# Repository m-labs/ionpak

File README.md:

ionpak
======

A modern, low-cost universal controller for hot-cathode ionization vacuum gauges.

Why?
----

Many physics experiments require a good vacuum and therefore tools to diagnose vacuum-related problems. Ionization gauges provide a way to measure pressures in the medium to ultra-high vacuum regimes.

While the gauges themselves can be procured quite easily, the controller situation is more problematic. Existing commercial and DIY solutions have one or more of the following issues:

 * expensive
 * proprietary
 * poor performance at low (pA) collector currents
 * designed with obsolete components and overly bulky
 * lack of gauge voltage/current programmability
 * no/poor connectivity to a logging database
 * poor design and construction

The ionpak features:

 * a single-board low-cost design with modern components
 * open hardware and software
 * sub-pA electrometer performance
 * configurable voltages and emission current to adapt to various gauges
 * Ethernet connectivity

Where to find ionization vacuum gauges?
---------------------------------------

For medium and high vacuum, Chinese gauges can be ordered on Taobao under references ZJ-27 and ZJ-10. The Chinese for ionization gauge is 电离规. Those gauges have a simple construction and an extremely low cost, under USD 10 for glass tubulated models (requires flameworking) and a few times that price for flange-mounted ones. Those manufactured by [Chengdu Zhenghua](http://www.zhvacuum.com) appear to work satisfactorily, and glass gauges arrive sealed under vacuum (around 10⁻⁵ to 10⁻⁶ mbar) so they can be tested immediately. Ceramic sockets for the gauges can often be ordered from the same Taobao vendor.

For ultra-high vacuum, you can use G8130 from KJLC, which is pricy but of excellent quality. There is a lower-cost Bayard-Alpert Chinese gauge ZJ-12, of dubious quality for those pressure ranges, and with 2.5x less sensitivity than the KJLC part.

A low-cost source of quality UHV gauges remains to be found. You can try eBay, but the condition of the items is highly random.

How to connect the gauge?
-------------------------

The collector must be connected with a shielded (e.g. coaxial) cable. If the gauge has a metallic body (e.g. gauges mounted on CF flanges), connect the shield of the cable to the body, so that current from the high voltage electrodes will not leak into the collector electrode. This should not cause any ground loop in your system, as the gauge circuits inside the ionpak are galvanically isolated from its power input and from its Ethernet connector.

If a single cable is used for the filament and anode connections, the anode wire must be particularly well insulated from the filament wires, to avoid leakage currents that can be significant when the gauge is operated with a low emission (100µA or less) and influence the measurement result.

"Domino" terminal blocks from the local hardware store, with the plastic removed, can be used to connect the cables to the pins of CF-flanged gauges. Female circular contacts, such as Amphenol AT62-16-0122, are a nicer alternative but are slightly harder to find.

For baked systems, use PTFE insulated cables that can withstand 200°C. Operating the gauge during bake-out can remove the need to degas it (see the paper [Comments on the stability of B-A ionization gages](https://www.nist.gov/sites/default/files/documents/calibrations/jv13-2.pdf)).

It is a good idea to attach the cables to the vacuum system with a strap to avoid damaging the gauge by accidentally pulling on the cables, and to place a cover onto the pins to reduce the electrical shock hazard from the high voltage. Preferably those items should be made of metal so that they can be left on during bakeout.

Using the ionpak
----------------
Connect the ionpak to a firewalled Ethernet network *only*, as it does not provide authentication over the network.

The ionpak has a static IP address that defaults to `192.168.69.1`. It has a self-explanatory web interface that you can access by pointing your browser to [http://192.168.69.1](http://192.168.69.1). By default, the controller is disabled and the ionpak will not produce any output voltages; use the web interface to input your gauge settings and enable the controller.

The IP address, along with all the other configuration options, can be reset to the defaults by holding the pushbutton while the ionpak is powering up. The status LED will flash rapidly to acknowledge the configuration reset.

In addition to displaying its measurement results in the web interface, the ionpak exports them in the JSON format. The results are very straightforward to access from Python:

```
>>> import requests
>>> import json
>>> json.loads(requests.get("http://192.168.69.1/measure.json").text)
{'pressure': 3.8e-06, 'current': 3.357e-08}
```

In the JSON document, `pressure` is expressed in millibars and `current` (through the collector input) is expressed in amperes.

Warning
-------

Ionization gauges use dangerous voltages and the ionpak is capable of delivering a lethal amount of power. Be careful and use at your own risk.

Building and loading the firmware
---------------------------------

```sh
cd firmware
cargo build --release
openocd -f openocd.cfg
```

License
-------

Copyright 2017 M-Labs Limited.

License TBD, probably will be CERN OHL and GPL.

Pictures in the ``pictures`` folder, except ``proto_rev1.jpg``, are copyright Michelle Poon and not free.

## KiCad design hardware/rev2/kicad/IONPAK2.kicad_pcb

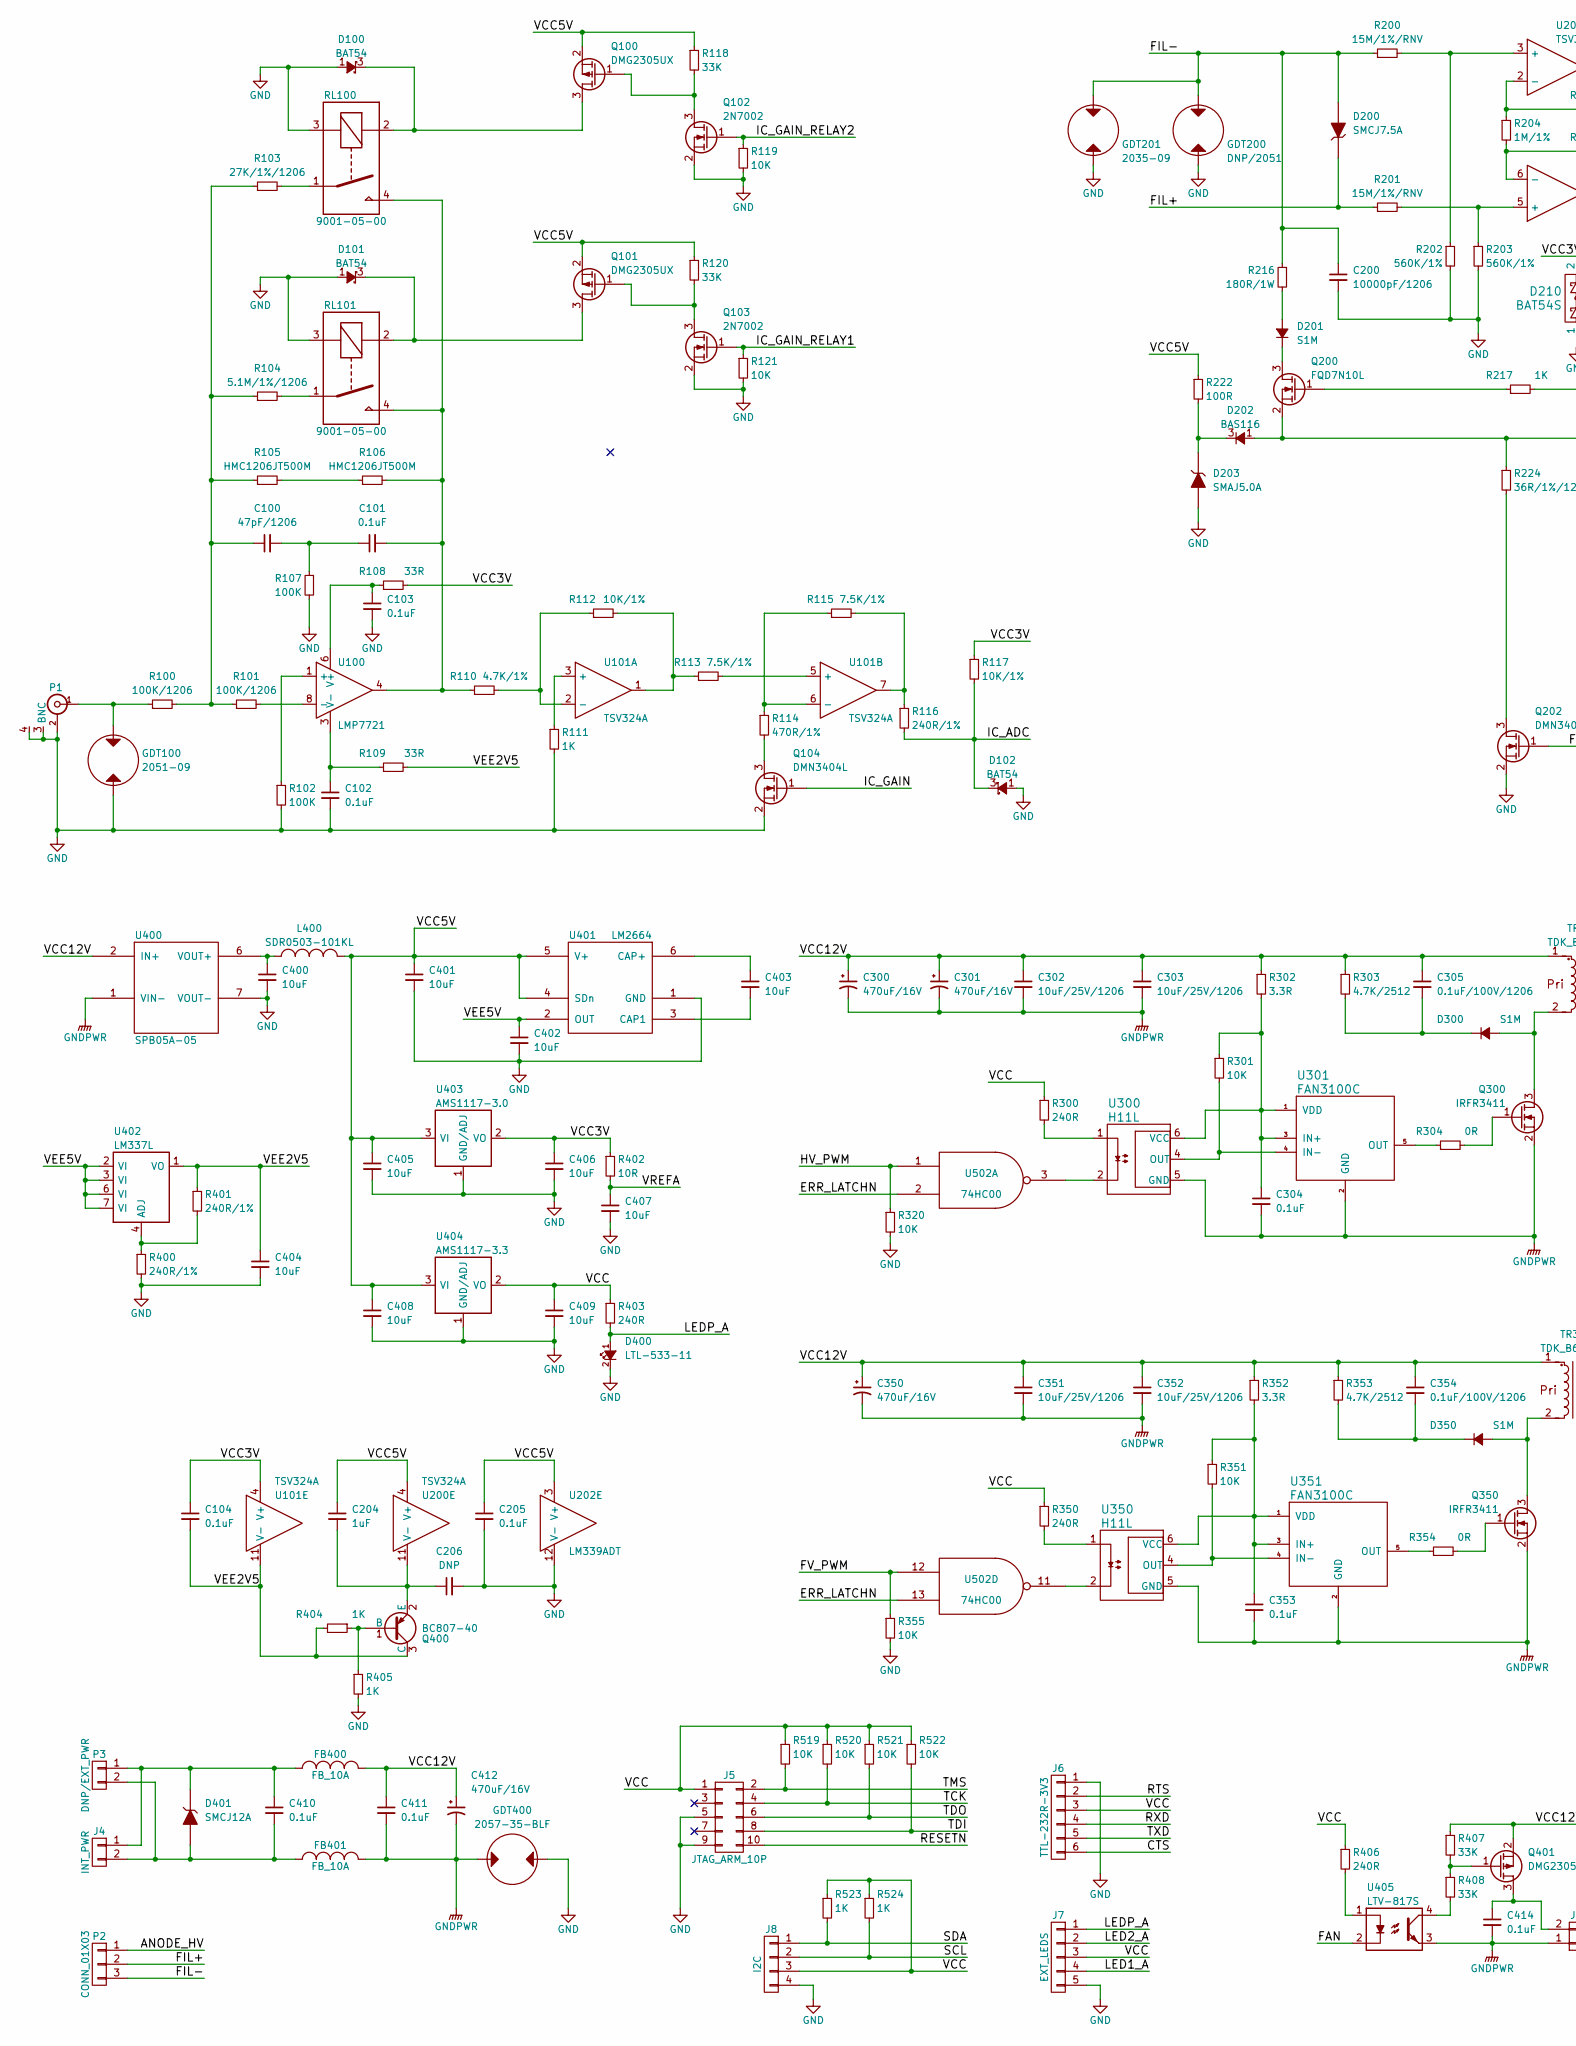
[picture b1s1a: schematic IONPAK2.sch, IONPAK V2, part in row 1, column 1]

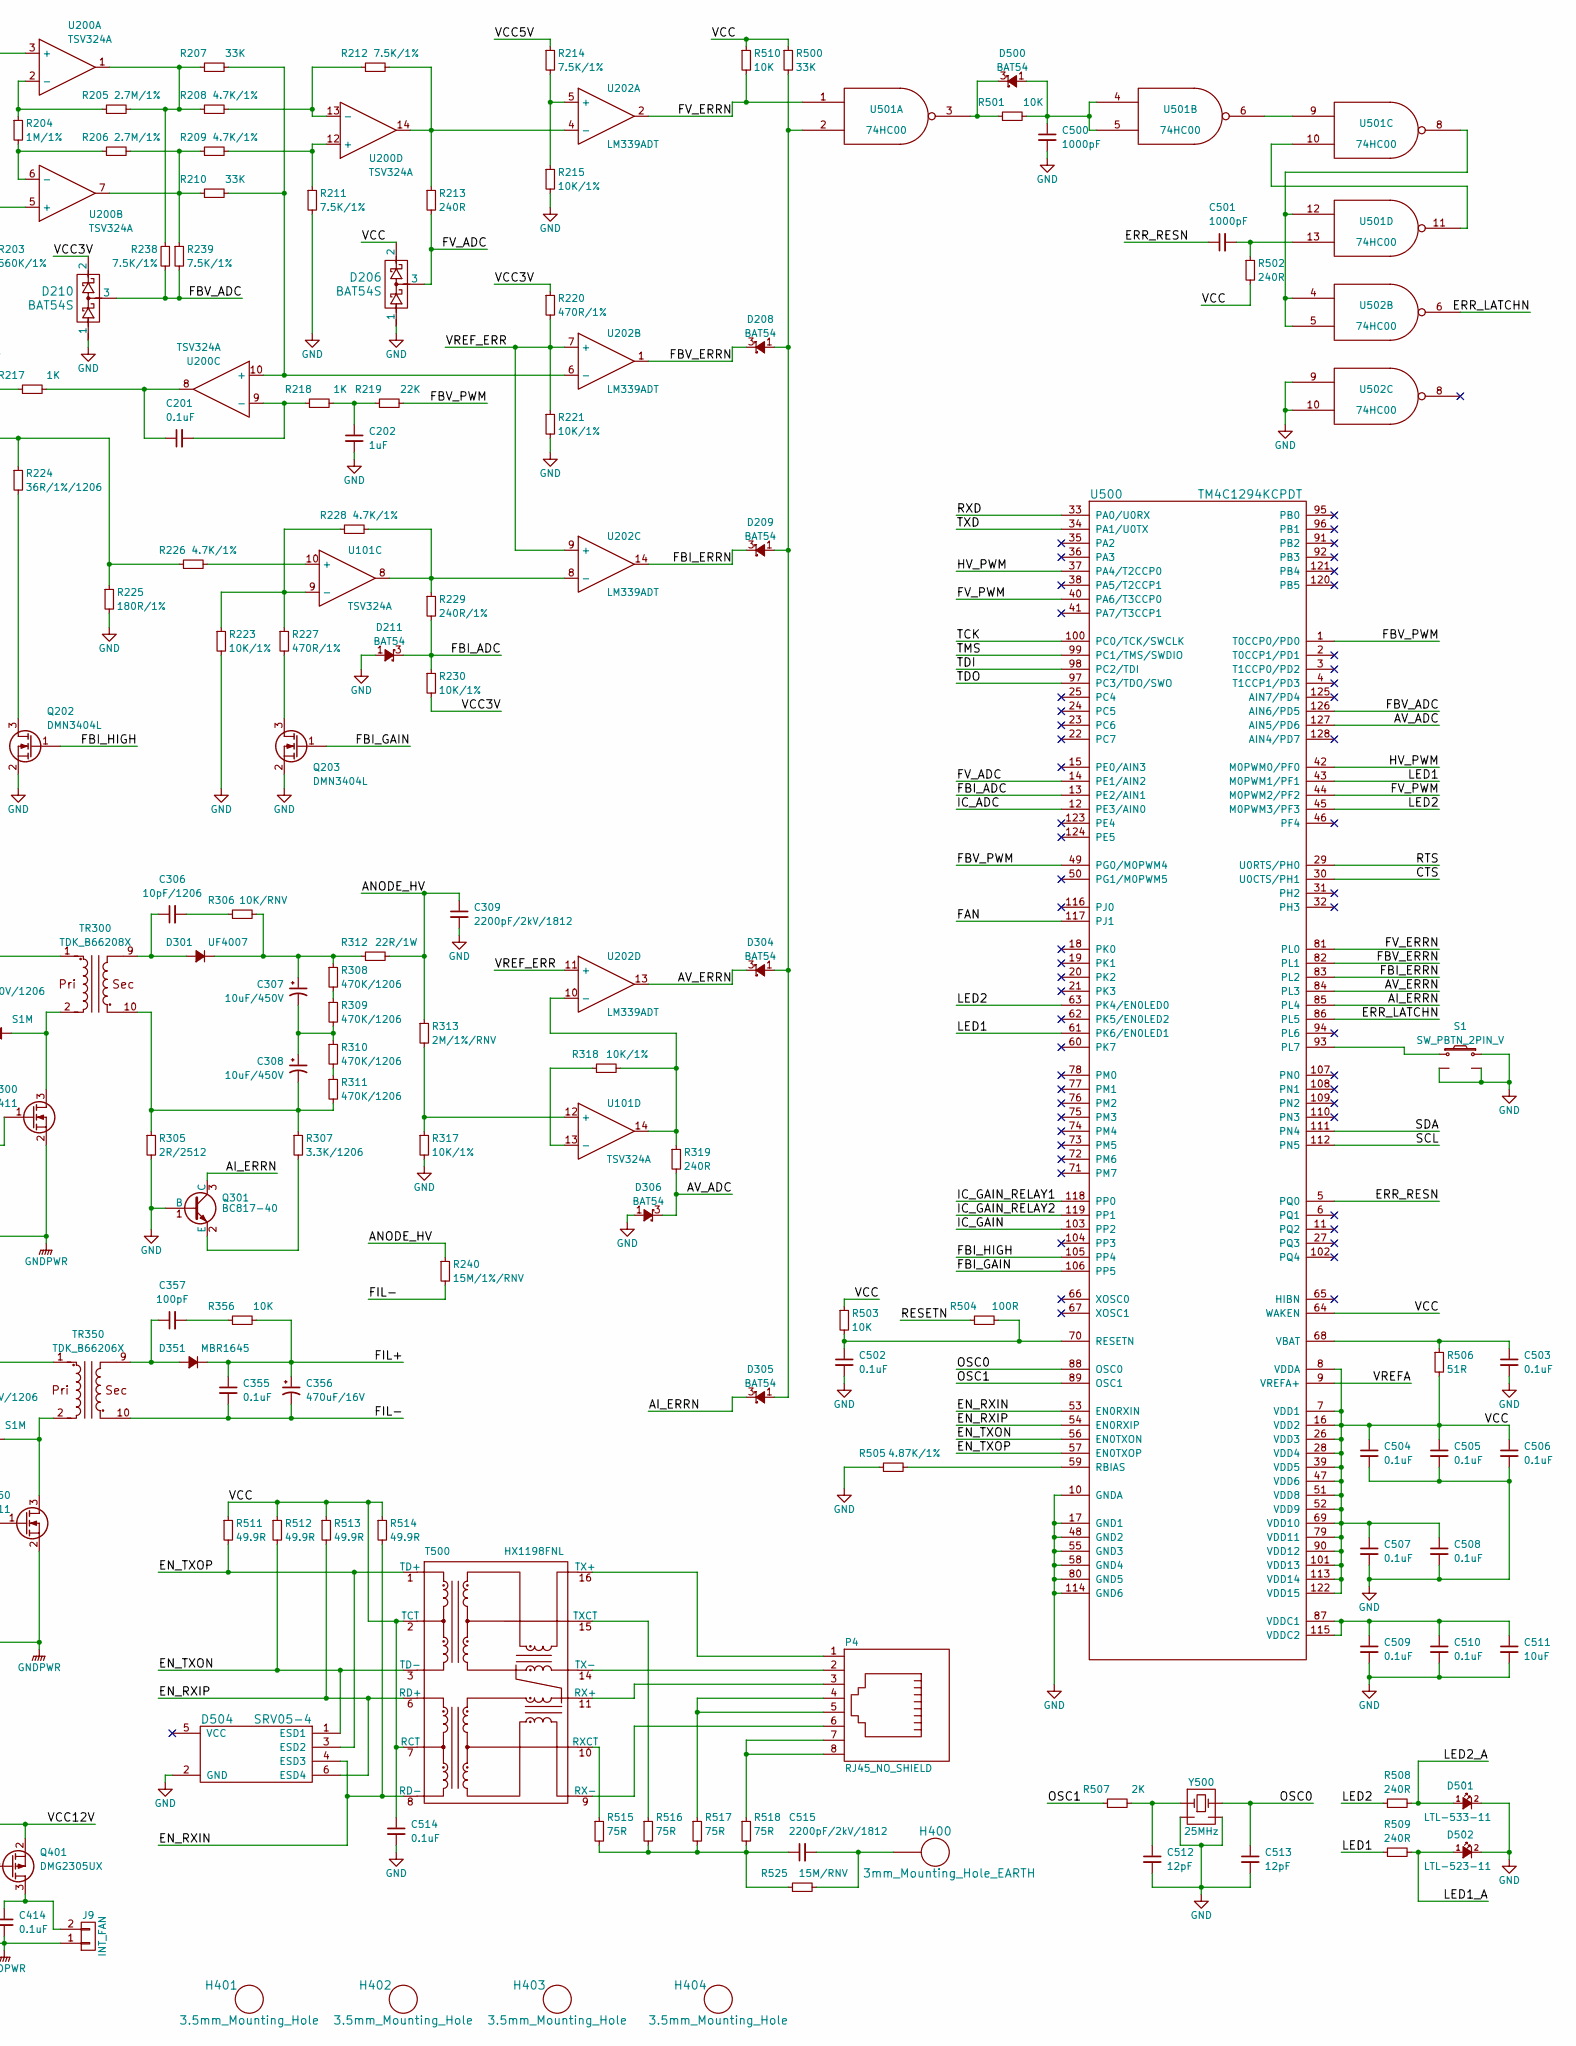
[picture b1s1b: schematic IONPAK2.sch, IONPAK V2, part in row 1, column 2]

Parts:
C100: 47pF/1206; C_1206_ns; MPN 12062A101JAT2A
C101, C102, C103, C104, C201, C205, C304, C353, C355, C410, C411, C414, C502, C503, C504, C505, C506, C507, C508, C509, C510, C514: 0.1uF; C_0603; MPN GRM188R71C104JA01D
C200: 10000pF/1206; C_1206; MPN GRM31BR72J103KW01L
C202, C204: 1uF; C_0603; MPN GRM188R60J105KA01J
C206: DNP; C_0603
C300, C301, C350, C356, C412: 470uF/16V; C_Radial_D13_L21_P5; MPN ECA-1CM471
C302, C303, C351, C352: 10uF/25V/1206; C_1206; MPN CL31A106KAHNNNE
C305, C354: 0.1uF/100V/1206; C_1206; MPN GRJ319R72A104KE11L
C306: 10pF/1206; C_1206; MPN CL31C100JIFNNNE
C307, C308: 10uF/450V; C_Radial_D14_L25_P5; MPN UVR2W100MHD1TO
C309, C515: 2200pF/2kV/1812; C_1812; MPN C1812C222KGRACTU
C357: 100pF; C_0603; MPN GRM0335C1E101JA01D
C400, C401, C402, C403, C404, C405, C406, C407, C408, C409, C511: 10uF; C_0603; MPN GRM188R60J106KE47D
C500, C501: 1000pF; C_0603; MPN GRM033R71C102KA01D
C512, C513: 12pF; C_0603; MPN GRM0335C1E120JA01D
D100, D101, D102, D208, D209, D211, D304, D305, D306, D500: BAT54; SOT-23; MPN BAT54SLT1G
D200: SMCJ7.5A; DO-214AB; MPN SMCJ7.5A-13-F
D201, D300, D350: S1M; DO-214AC; MPN S1MTR
D202: BAS116; SOT-23; MPN BAS116-7-F
D203: SMAJ5.0A; DO-214AC; MPN SMAJ5.0A
D206, D210: BAT54S; SOT-23; MPN BAT54SLT1G
D301: UF4007; Diode_DO-41_SOD81_Horizontal_RM10; MPN UF4007TA
D351: MBR1645; TO220AC; MPN MBR1060
D400, D501: LTL-533-11; LED_D3.0mm_Horizontal_O3.81mm_Z10.0mm; MPN LTL-533-11
D401: SMCJ12A; DO-214AB; MPN SMCJ12A-13-F
D502: LTL-523-11; LED_D3.0mm_Horizontal_O3.81mm_Z10.0mm; MPN LTL-523-11
D504: SRV05-4; SOT-23-6; MPN SRV05-4ATR
FB400, FB401: FB_10A; 28F0121-0SR-10; MPN 28F0121-0SR-10
GDT100: 2051-09; BOURNS-GDT-2051_ns; MPN 2051-09-SM-RPLF
GDT200: DNP/2051; BOURNS-GDT-2051
GDT201: 2035-09; BOURNS-GDT-2035TH; MPN 2035-09-BT1LF
GDT400: 2057-35-BLF; BOURNS-GDT-2035TH; MPN 2057-35-BLF
H400: 3mm_Mounting_Hole_EARTH; 3mm_EARTH
H401, H402, H403, H404: 3.5mm_Mounting_Hole; NPTH_3mm5_ID
J4: INT_PWR; PhoenixContact_MCV-G_02x5.08mm_Vertical; MPN 1836299
J5: JTAG_ARM_10P; Pin_Header_Straight_2x05_Pitch1.27mm; MPN GRPB052VWVN-RC
J6: TTL-232R-3V3; Pin_Header_Straight_1x06_Pitch2.54mm; MPN SWR25X-NRTC-S06-ST-BA
J7: EXT_LEDS; Pin_Header_Straight_1x05_Pitch2.54mm; MPN SWR25X-NRTC-S04-ST-BA
J8: I2C; Pin_Header_Straight_1x04_Pitch2.54mm
J9: INT_FAN; Molex_KK-6410-02_02x2.54mm_Straight; MPN 0022272021
L400: SDR0503-101KL; Choke_SMD_Wuerth-WE-PD2-Typ-MS; MPN SDR0503-101KL
P1: BNC; bnc_90_1-1337543-0_ns; MPN 1-1337543-0
P2: CONN_01X03; PhoenixContact_1786417_03; MPN 1786417
P3: DNP/EXT_PWR; PhoenixContact_MSTBA-G_02x5.08mm_Angled
P4: RJ45_NO_SHIELD; FCI_54601-908WPLF; MPN 54601-908WPLF
Q100, Q101, Q401: DMG2305UX; SOT-23; MPN DMG2305UX-13
Q102, Q103: 2N7002; SOT-23; MPN 2N7002P,215
Q104, Q202, Q203: DMN3404L; SOT-23; MPN DMN3404L-7
Q200: FQD7N10L; DPAK; MPN FQD7N10LTM
Q300, Q350: IRFR3411; DPAK; MPN IRFR3411TRPBF
Q301: BC817-40; SOT-23; MPN BC81740MTF
Q400: BC807-40; SOT-23; MPN BC807-40LT1G
R100, R101: 100K/1206; R_1206_ns; MPN RC1206JR-07100KL
R102, R107: 100K; R_0603; MPN RC0603JR-07100KL
R103: 27K/1%/1206; R_1206_ns; MPN RC1206FR-0727KL
R104: 5.1M/1%/1206; R_1206_ns; MPN RC1206FR-0727KL
R105, R106: HMC1206JT500M; R_1206_ns; MPN HMC1206JT500M
R108, R109: 33R; R_0603; MPN RC0603FR-0733RL
R110, R208, R209, R226, R228: 4.7K/1%; R_0603; MPN RC0603FR-074K7L
R111, R217, R218, R404, R405, R523, R524: 1K; R_0603; MPN RC0603FR-071KL
R112, R117, R215, R221, R223, R230, R317, R318: 10K/1%; R_0603; MPN RC0603FR-0710KL
R113, R115, R211, R212, R214, R238, R239: 7.5K/1%; R_0603; MPN RC0603FR-077K5L
R114, R220, R227: 470R/1%; R_0603; MPN RC0603FR-07470RL
R116, R229, R400, R401: 240R/1%; R_0603; MPN RC0603FR-07240RL
R118, R120, R207, R210, R407, R408, R500: 33K; R_0603; MPN RC0603FR-0733KL
R119, R121, R301, R320, R351, R355, R356, R501, R503, R510, R519, R520, R521, R522: 10K; R_0603; MPN RC0603FR-0710KL
R200, R201, R240: 15M/1%/RNV; R_Axial_DIN0207_L6.3mm_D2.5mm_P10.16mm_Horizontal; MPN RNV14FAL15M0
R202, R203: 560K/1%; R_0603; MPN RC0603FR-07560KL
R204: 1M/1%; R_0603; MPN RC0603FR-071ML
R205, R206: 2.7M/1%; R_0603; MPN RC0603FR-072M7L
R213, R300, R319, R350, R403, R406, R502, R508, R509: 240R; R_0603; MPN RC0603FR-07240RL
R216: 180R/1W; R_Axial_DIN0414_L11.9mm_D4.5mm_P15.24mm_Horizontal; MPN KNP100JR-73-180R
R219: 22K; R_0603; MPN RC0603FR-0722KL
R222, R504: 100R; R_0603; MPN RC0603JR-07100RL
R224: 36R/1%/1206; R_1206; MPN RC1206FR-0736RL
R225: 180R/1%; R_0603; MPN RC0603FR-07180RL
R302, R352: 3.3R; R_0603; MPN RC0603FR-073R3L
R303, R353: 4.7K/2512; R_2512; MPN RC2512JK-074K7L
R304, R354: 0R; R_0603; MPN RC0603JR-070RL
R305: 2R/2512; R_2512; MPN RMCF2512JT2R00
R306: 10K/RNV; R_Axial_DIN0207_L6.3mm_D2.5mm_P10.16mm_Horizontal; MPN RNF14FTD10K0
R307: 3.3K/1206; R_1206; MPN RC1206JR-073K3L
R308, R309, R310, R311: 470K/1206; R_1206; MPN RC1206JR-07470KL
R312: 22R/1W; R_Axial_DIN0414_L11.9mm_D4.5mm_P15.24mm_Horizontal; MPN KNP100JR-73-22R
R313: 2M/1%/RNV; R_Axial_DIN0207_L6.3mm_D2.5mm_P10.16mm_Horizontal; MPN RNV14FAL2M00
R402: 10R; R_0603; MPN RC0603JR-0710RL
R505: 4.87K/1%; R_0603; MPN RC0603FR-074K87L
R506: 51R; R_0603; MPN RC0603FR-0751RL
R507: 2K; R_0603; MPN RC0603FR-072KL
R511, R512, R513, R514: 49.9R; R_0603; MPN RC0603FR-0749R9L
R515, R516, R517, R518: 75R; R_0603; MPN 311-75.0HRCT-ND
R525: 15M/RNV; R_Axial_DIN0207_L6.3mm_D2.5mm_P10.16mm_Horizontal; MPN RNV14FAL15M0
RL100, RL101: 9001-05-00; COTO-9001_ns; MPN 9001-05-00
S1: SW_PBTN_2PIN_V; SW_Tactile_SKHH_Angled_v; MPN 1825027-8
T500: HX1198FNL; H2019FNL; MPN HX1198FNL
TR300: TDK_B66208X; MPN TranformerFl
TR350: TDK_B66206X; MPN TransformerHV
U100: LMP7721; SOIC-8-N_ns; MPN LMP7721MA/NOPB
U101, U200: TSV324A; SOIC-14_N; MPN TSV324IDT
U202: LM339ADT; SOIC-14_N; MPN LM339ADT
U300, U350: H11L; 6-SMD; MPN H11L1S(TA)
U301, U351: FAN3100C; SOT-23-5; MPN FAN3100CSX
U400: SPB05A-05; SPB05A; MPN SPB05A-05
U401: LM2664; SOT-23-6; MPN LM2664M6/NOPB
U402: LM337L; SOIC-8-N; MPN LM337LMX
U403: AMS1117-3.0; SOT-223; MPN TLV1117LV30DCYR
U404: AMS1117-3.3; SOT-223; MPN AZ1117IH-3.3TRG1
U405: LTV-817S; OPTO-SMD4; MPN LTV-817S-TA1
U500: TM4C1294KCPDT; TQFP-128; MPN TM4C1294KCPDTI3R
U501, U502: 74HC00; SOIC-14_N; MPN 74HC00S14-13
Y500: 25MHz; XTAL3_2X2_5; MPN NX3225GA-25.000M-STD-CRG-2

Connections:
/AI_ERRN: D305.3 (K), Q301.3 (C), U500.85 (PL4)
/ANODE_HV: C309.1, P2.1, R240.1, R312.2, R313.1
/AV_ADC: D306.3 (K), R319.2, U500.127 (AIN5/PD6)
/AV_ERRN: D304.3 (K), U202.13, U500.84 (PL3)
/CTS: J6.6, U500.30 (U0CTS/PH1)
/EN_RXIN: D504.4 (ESD3), R514.2, T500.8 (RD-), U500.53 (EN0RXIN)
/EN_RXIP: D504.6 (ESD4), R513.2, T500.6 (RD+), U500.54 (EN0RXIP)
/EN_TXON: D504.1 (ESD1), R512.2, T500.3 (TD-), U500.56 (EN0TXON)
/EN_TXOP: D504.3 (ESD2), R511.2, T500.1 (TD+), U500.57 (EN0TXOP)
/ERR_LATCHN: U500.86 (PL5), U502.2, U502.6, U502.13
/ERR_RESN: C501.1, U500.5 (PQ0)
/FAN: U405.2, U500.117 (PJ1)
/FBI_ADC: D211.3 (K), R229.2, R230.1, U500.13 (PE2/AIN1)
/FBI_ERRN: D209.3 (K), U202.14, U500.83 (PL2)
/FBI_GAIN: Q203.1 (G), U500.106 (PP5)
/FBI_HIGH: Q202.1 (G), U500.105 (PP4)
/FBV_ADC: D210.3, R238.2, R239.2, U500.126 (AIN6/PD5)
/FBV_ERRN: D208.3 (K), U202.1, U500.82 (PL1)
/FBV_PWM: R219.2, U500.1 (T0CCP0/PD0), U500.49 (PG0/M0PWM4)
/FIL+: C355.1, C356.1, D200.1 (K), D351.1 (K), P2.2, R201.1, R356.2
/FIL-: C200.1, C355.2, C356.2, D200.2 (A), GDT200.1, GDT201.1, P2.3, R200.1, R216.1, R240.2, TR350.10
/FV_ADC: D206.3, R213.2, U500.14 (PE1/AIN2)
/FV_ERRN: R510.2, U202.2, U500.81 (PL0), U501.1
/FV_PWM: R355.1, U500.40 (PA6/T3CCP0), U500.44 (M0PWM2/PF2), U502.12
/HV_PWM: R320.1, U500.37 (PA4/T2CCP0), U500.42 (M0PWM0/PF0), U502.1
/IC_ADC: D102.3 (K), R116.2, R117.2, U500.12 (PE3/AIN0)
/IC_GAIN: Q104.1 (G), U500.103 (PP2)
/IC_GAIN_RELAY1: Q103.1 (G), R121.1, U500.118 (PP0)
/IC_GAIN_RELAY2: Q102.1 (G), R119.1, U500.119 (PP1)
/LED1: R509.1, U500.43 (M0PWM1/PF1), U500.61 (PK6/EN0LED1)
/LED1_A: D502.1 (A), J7.4, R509.2
/LED2: R508.1, U500.45 (M0PWM3/PF3), U500.63 (PK4/EN0LED0)
/LED2_A: D501.1 (A), J7.2, R508.2
/LEDP_A: D400.1 (A), J7.1, R403.2
/OSC0: C513.1, U500.88 (OSC0), Y500.3
/OSC1: R507.1, U500.89 (OSC1)
/RESETN: J5.10, R504.1
/RTS: J6.2, U500.29 (U0RTS/PH0)
/RXD: J6.4, U500.33 (PA0/U0RX)
/SCL: J8.2, R524.2, U500.112 (PN5)
/SDA: J8.1, R523.2, U500.111 (PN4)
/TCK: J5.4, R520.2, U500.100 (PC0/TCK/SWCLK)
/TDI: J5.8, R522.2, U500.98 (PC2/TDI)
/TDO: J5.6, R521.2, U500.97 (PC3/TDO/SWO)
/TMS: J5.2, R519.2, U500.99 (PC1/TMS/SWDIO)
/TXD: J6.5, U500.34 (PA1/U0TX)
/VCC3V: C104.1, C406.1, D210.2, R108.2, R117.1, R220.1, R230.2, R402.1, U101.4 (V+), U403.2 (VO)
/VCC5V: C204.1, C205.1, C401.1, C405.1, C408.1, L400.2, Q100.2 (S), Q101.2 (S), R118.1, R120.1, R214.1, R222.1, U200.4 (V+), U202.3 (V+), U401.4 (SDn), U401.5 (V+), U403.3 (VI), U404.3 (VI)
/VCC12V: C300.1, C301.1, C302.1, C303.1, C305.1, C350.1, C351.1, C352.1, C354.1, C411.1, C412.1, FB400.2, Q401.2 (S), R302.1, R303.1, R352.1, R353.1, R407.1, TR300.1, TR350.1, U400.2 (IN+)
/VEE2V5: C104.2, C404.1, Q400.3 (C), R109.2, R401.1, R404.2, U101.11 (V-), U402.1 (VO)
/VEE5V: C402.1, U401.2 (OUT), U402.2 (VI), U402.3 (VI), U402.6 (VI), U402.7 (VI)
/VREFA: C407.1, R402.2, U500.9 (VREFA+)
/VREF_ERR: R220.2, R221.1, U202.7 (+), U202.9 (+), U202.11 (+)
GND: C102.2, C103.2, C200.2, C202.2, C205.2, C206.2, C309.2, C400.2, C401.2, C402.2, C404.2, C405.2, C406.2, C407.2, C408.2, C409.2, C500.2, C502.2, C503.2, C504.2, C505.2, C506.2, C507.2, C508.2, C509.2, C510.2, C511.2, C512.2, C513.2, C514.2, D100.1 (A), D101.1 (A), D102.1 (A), D203.2 (A), D206.1, D210.1, D211.1 (A), D306.1 (A), D400.2 (K), D501.2 (K), D502.2 (K), D504.2 (GND), GDT100.2, GDT200.2, GDT201.2, GDT400.1, J5.5, J5.9, J6.1, J7.5, J8.4, P1.2 (Ext), P1.3 (M1), P1.4 (M2), Q102.2 (S), Q103.2 (S), Q104.2 (S), Q202.2 (S), Q203.2 (S), Q301.1 (B), R102.2, R107.2, R111.2, R119.2, R121.2, R202.2, R203.2, R211.2, R215.2, R221.2, R223.2, R225.2, R305.2, R317.2, R320.2, R355.2, R400.2, R405.2, R505.1, RL100.3, RL101.3, S1.2, S1.3 (GND), S1.4 (GND), U100.2 (GND), U100.7 (GND), U202.12 (V-), U400.7 (VOUT-), U401.1 (GND), U403.1 (GND/ADJ), U404.1 (GND/ADJ), U500.10 (GNDA), U500.17 (GND1), U500.48 (GND2), U500.55 (GND3), U500.58 (GND4), U500.80 (GND5), U500.114 (GND6), U501.7 (GND), U502.7 (GND), U502.9, U502.10, Y500.2 (GND), Y500.4 (GND)
GNDPWR: C300.2, C301.2, C302.2, C303.2, C304.2, C350.2, C351.2, C352.2, C353.2, C411.2, C412.2, C414.2, FB401.2, GDT400.2, J9.1, Q300.2 (S), Q350.2 (S), U300.5 (GND), U301.2 (GND), U350.5 (GND), U351.2 (GND), U400.1 (VIN-), U405.3
unnamed: C100.1, R100.2, R101.1, R103.1, R104.1, R105.1
unnamed: C100.2, C101.1, R107.1
unnamed: C101.2, R106.2, R110.1, RL100.4, RL101.4, U100.4
unnamed: C102.1, R109.1, U100.3 (V-)
unnamed: C103.1, R108.1, U100.6 (V+)
unnamed: C201.1, R217.2, U200.8
unnamed: C201.2, R218.1, U200.9 (-)
unnamed: C202.1, R218.2, R219.1
unnamed: C204.2, C206.1, Q400.2 (E), U200.11 (V-)
unnamed: C304.1, R301.1, R302.2, U300.6 (VCC), U301.1 (VDD), U301.3 (IN+)
unnamed: C305.2, D300.1 (K), R303.2
unnamed: C306.1, D301.2 (A), TR300.9
unnamed: C306.2, R306.1
unnamed: C307.1, D301.1 (K), R306.2, R308.1, R312.1
unnamed: C307.2, C308.1, R309.2, R310.1
unnamed: C308.2, R305.1, R307.1, R311.2, TR300.10
unnamed: C353.1, R351.1, R352.2, U350.6 (VCC), U351.1 (VDD), U351.3 (IN+)
unnamed: C354.2, D350.1 (K), R353.2
unnamed: C357.1, D351.2 (A), TR350.9
unnamed: C357.2, R356.1
unnamed: C400.1, L400.1, U400.6 (VOUT+)
unnamed: C403.1, U401.6 (CAP+)
unnamed: C403.2, U401.3 (CAP1)
unnamed: C410.1, D401.1 (K), FB400.1, J4.1, P3.1
unnamed: C410.2, D401.2 (A), FB401.1, J4.2, P3.2
unnamed: C414.1, J9.2, Q401.3 (D)
unnamed: C500.1, D500.1 (A), R501.2, U501.4, U501.5
unnamed: C501.2, R502.1, U501.13
unnamed: C502.1, R503.2, R504.2, U500.70 (RESETN)
unnamed: C503.1, R506.1, U500.68 (VBAT)
unnamed: C509.1, C510.1, C511.1, U500.87 (VDDC1), U500.115 (VDDC2)
unnamed: C512.1, R507.2, Y500.1
unnamed: C515.1, R515.2, R516.2, R517.2, R518.2, R525.1
unnamed: C515.2, H400.1, R525.2
unnamed: D100.3 (K), Q100.3 (D), RL100.2
unnamed: D101.3 (K), Q101.3 (D), RL101.2
unnamed: D201.1 (K), Q200.3 (D)
unnamed: D201.2 (A), R216.2
unnamed: D202.1 (A), Q200.2 (S), R224.1, R225.1, R226.1
unnamed: D202.3 (K), D203.1 (K), R222.2
unnamed: D208.1 (A), D209.1 (A), D304.1 (A), D305.1 (A), R500.2, U501.2
unnamed: D300.2 (A), Q300.3 (D), TR300.2
unnamed: D350.2 (A), Q350.3 (D), TR350.2
unnamed: D500.3 (K), R501.1, U501.3
unnamed: GDT100.1, P1.1 (In), R100.1
unnamed: P4.1, T500.16 (TX+)
unnamed: P4.2, T500.14 (TX-)
unnamed: P4.3, T500.11 (RX+)
unnamed: P4.4, P4.5, R517.1
unnamed: P4.6, T500.9 (RX-)
unnamed: P4.7, P4.8, R518.1
unnamed: Q100.1 (G), Q102.3 (D), R118.2
unnamed: Q101.1 (G), Q103.3 (D), R120.2
unnamed: Q104.3 (D), R114.2
unnamed: Q200.1 (G), R217.1
unnamed: Q202.3 (D), R224.2
unnamed: Q203.3 (D), R227.2
unnamed: Q300.1 (G), R304.2
unnamed: Q301.2 (E), R307.2
unnamed: Q350.1 (G), R354.2
unnamed: Q400.1 (B), R404.1, R405.1
unnamed: Q401.1 (G), R407.2, R408.1
unnamed: R101.2, U100.8 (-)
unnamed: R102.1, U100.1 (+)
unnamed: R103.2, RL100.1
unnamed: R104.2, RL101.1
unnamed: R105.2, R106.1
unnamed: R110.2, R112.1, U101.2 (-)
unnamed: R111.1, U101.3 (+)
unnamed: R112.2, R113.1, U101.1
unnamed: R113.2, U101.5 (+)
unnamed: R114.1, R115.1, U101.6 (-)
unnamed: R115.2, R116.1, U101.7
unnamed: R200.2, R202.1, U200.3 (+)
unnamed: R201.2, R203.1, U200.5 (+)
unnamed: R204.1, R205.1, U200.2 (-)
unnamed: R204.2, R206.1, U200.6 (-)
unnamed: R205.2, R207.1, R208.1, R238.1, U200.1
unnamed: R206.2, R209.1, R210.1, R239.1, U200.7
unnamed: R207.2, R210.2, U200.10 (+), U202.6 (-)
unnamed: R208.2, R212.1, U200.13 (-)
unnamed: R209.2, R211.1, U200.12 (+)
unnamed: R212.2, R213.1, U200.14, U202.4 (-)
unnamed: R214.2, R215.1, U202.5 (+)
unnamed: R223.1, R227.1, R228.1, U101.9 (-)
unnamed: R226.2, U101.10 (+)
unnamed: R228.2, R229.1, U101.8, U202.8 (-)
unnamed: R300.2, U300.1
unnamed: R301.2, U300.4 (OUT), U301.4 (IN-)
unnamed: R304.1, U301.5 (OUT)
unnamed: R308.2, R309.1
unnamed: R310.2, R311.1
unnamed: R313.2, R317.1, U101.12 (+)
unnamed: R318.1, U101.13 (-)
unnamed: R318.2, R319.1, U101.14, U202.10 (-)
unnamed: R350.2, U350.1
unnamed: R351.2, U350.4 (OUT), U351.4 (IN-)
unnamed: R354.1, U351.5 (OUT)
unnamed: R400.1, R401.2, U402.4 (ADJ)
unnamed: R406.2, U405.1
unnamed: R408.2, U405.4
unnamed: R505.2, U500.59 (RBIAS)
unnamed: R515.1, T500.10 (RXCT)
unnamed: R516.1, T500.15 (TXCT)
unnamed: S1.1, U500.93 (PL7)
unnamed: U300.2, U502.3
unnamed: U350.2, U502.11
unnamed: U501.6, U501.9
unnamed: U501.10, U501.11
unnamed: U501.8, U501.12, U502.4, U502.5
VCC: C409.1, C504.1, C505.1, C506.1, C507.1, C508.1, C514.1, D206.2, J5.1, J6.3, J7.3, J8.3, R300.1, R350.1, R403.1, R406.1, R500.1, R502.2, R503.1, R506.2, R510.1, R511.1, R512.1, R513.1, R514.1, R519.1, R520.1, R521.1, R522.1, R523.1, R524.1, T500.2 (TCT), T500.7 (RCT), U404.2 (VO), U500.7 (VDD1), U500.8 (VDDA), U500.16 (VDD2), U500.26 (VDD3), U500.28 (VDD4), U500.39 (VDD5), U500.47 (VDD6), U500.51 (VDD8), U500.52 (VDD9), U500.64 (WAKEN), U500.69 (VDD10), U500.79 (VDD11), U500.90 (VDD12), U500.101 (VDD13), U500.113 (VDD14), U500.122 (VDD15), U501.14 (VCC), U502.14 (VCC)

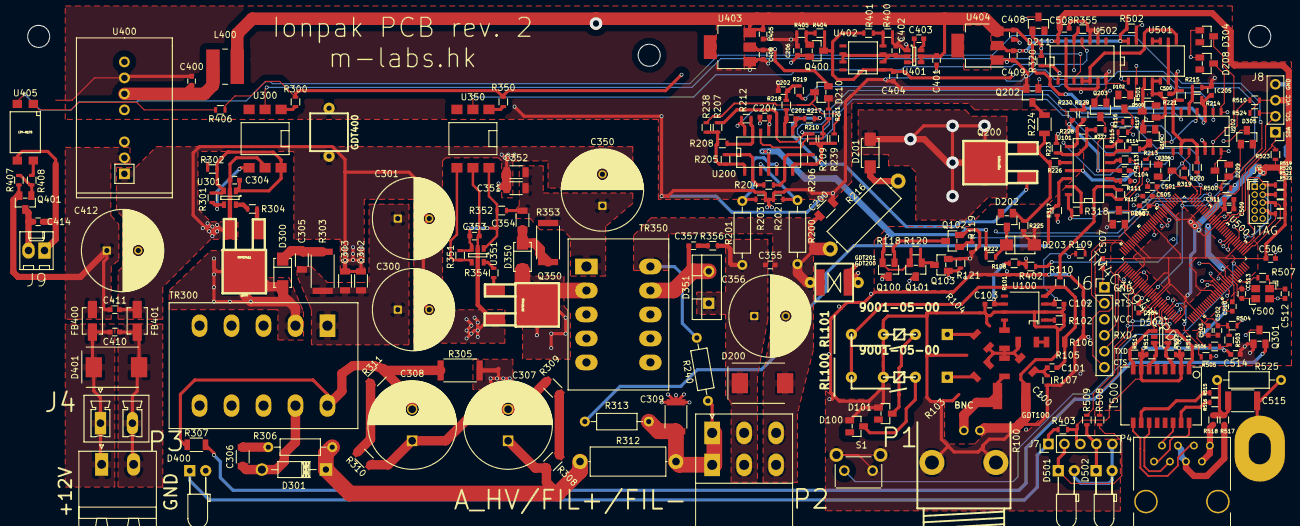
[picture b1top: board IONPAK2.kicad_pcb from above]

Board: 4 copper layers, 259 parts (0 on the bottom side), 166 nets.

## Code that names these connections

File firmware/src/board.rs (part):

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use tm4c129x;


const LED1: u8 = 0x10; // PK4
const LED2: u8 = 0x40; // PK6

const HV_PWM: u8 = 0x01;  // PF0
const FV_PWM: u8 = 0x04;  // PF2
const FBV_PWM: u8 = 0x01; // PD5

const FD_ADC: u8 = 0x01;  // PE0
const FV_ADC: u8 = 0x02;  // PE1
const FBI_ADC: u8 = 0x04; // PE2
const IC_ADC: u8 = 0x08;  // PE3
const FBV_ADC: u8 = 0x20; // PD5
const AV_ADC: u8 = 0x40;  // PD6

const FV_ERRN: u8 = 0x01;    // PL0
const FBV_ERRN: u8 = 0x02;   // PL1
const FBI_ERRN: u8 = 0x04;   // PL2
const AV_ERRN: u8 = 0x08;    // PL3
const AI_ERRN: u8 = 0x10;    // PL4
const ERR_LATCHN: u8 = 0x20; // PL5
const BTNN: u8 = 0x80;       // PL7
const ERR_RESN: u8 = 0x01;   // PQ0

const PWM_LOAD: u16 = (/*pwmclk*/120_000_000u32 / /*freq*/100_000) as u16;
const UART_DIV: u32 = (((/*sysclk*/120_000_000 * 8) / /*baud*/115200) + 1) / 2;
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    cortex_m::interrupt::free(|_cs| {
        let gpio_k = unsafe { &*tm4c129x::GPIO_PORTK::ptr() };
        if state {
            gpio_k.data.modify(|r, w| w.data().bits(r.data().bits() | LED2))
        } else {
            gpio_k.data.modify(|r, w| w.data().bits(r.data().bits() & !LED2))
        }
    });
}
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pub fn reset_error() {
    cortex_m::interrupt::free(|_cs| {
        let gpio_q = unsafe { &*tm4c129x::GPIO_PORTQ::ptr() };
        gpio_q.data.modify(|r, w| w.data().bits(r.data().bits() & !ERR_RESN));
        gpio_q.data.modify(|r, w| w.data().bits(r.data().bits() | ERR_RESN));
    });
}

pub fn error_latched() -> bool {
    cortex_m::interrupt::free(|_cs| {
        let gpio_l = unsafe { &*tm4c129x::GPIO_PORTL::ptr() };
        gpio_l.data.read().bits() as u8 & ERR_LATCHN == 0
    })
}

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        let gpio_l = unsafe { &*tm4c129x::GPIO_PORTL::ptr() };
        gpio_l.data.read().bits() as u8
    });
    if gpio_dat & FV_ERRN == 0 {
        println!("Filament overvolt");
    }
    if gpio_dat & FBV_ERRN == 0 {
        println!("Filament bias overvolt");
    }
    if gpio_dat & FBI_ERRN == 0 {
        println!("Filament bias overcurrent");
    }
    if gpio_dat & AV_ERRN == 0 {
        println!("Anode overvolt");
    }
    if gpio_dat & AI_ERRN == 0 {
        println!("Anode overcurrent");
    }
}
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
        // Set up LEDs
        let gpio_k = unsafe { &*tm4c129x::GPIO_PORTK::ptr() };
        gpio_k.dir.write(|w| w.dir().bits(LED1|LED2));
        gpio_k.den.write(|w| w.den().bits(LED1|LED2));
        // Switch LED1 to LAN mode
        gpio_k.afsel.modify(|_, w| w.afsel().bits(LED1));
        gpio_k.pctl.modify(|_, w| unsafe { w.pmc4().bits(5) }); // EN0LED0

        // Set up gain and emission range control pins
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        // Set up error and pushbutton pins
        let gpio_l = unsafe { &*tm4c129x::GPIO_PORTL::ptr() };
        let gpio_q = unsafe { &*tm4c129x::GPIO_PORTQ::ptr() };
        gpio_l.pur.write(|w| w.pue().bits(FV_ERRN|FBV_ERRN|FBI_ERRN|AV_ERRN|AI_ERRN|BTNN));
        gpio_l.den.write(|w| w.den().bits(FV_ERRN|FBV_ERRN|FBI_ERRN|AV_ERRN|AI_ERRN|ERR_LATCHN|BTNN));
        gpio_q.dir.write(|w| w.dir().bits(ERR_RESN));
        gpio_q.den.write(|w| w.den().bits(ERR_RESN));
        reset_error(); // error latch is an undefined state upon power-up; reset it

        // Set up PWMs
        let gpio_f = unsafe { &*tm4c129x::GPIO_PORTF_AHB::ptr() };
        gpio_f.dir.write(|w| w.dir().bits(HV_PWM|FV_PWM));
        gpio_f.den.write(|w| w.den().bits(HV_PWM|FV_PWM));
        gpio_f.afsel.write(|w| w.afsel().bits(HV_PWM|FV_PWM));
        gpio_f.pctl.write(|w| unsafe { w.pmc0().bits(6).pmc2().bits(6) });

        let gpio_g = unsafe { &*tm4c129x::GPIO_PORTG_AHB::ptr() };
        gpio_g.dir.write(|w| w.dir().bits(FBV_PWM));
        gpio_g.den.write(|w| w.den().bits(FBV_PWM));
        gpio_g.afsel.write(|w| w.afsel().bits(FBV_PWM));
        gpio_g.pctl.write(|w| unsafe { w.pmc0().bits(6) });

        sysctl.rcgcpwm.modify(|_, w| w.r0().bit(true));
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
        let gpio_d = unsafe { &*tm4c129x::GPIO_PORTD_AHB::ptr() };
        let gpio_e = unsafe { &*tm4c129x::GPIO_PORTE_AHB::ptr() };
        gpio_d.afsel.write(|w| w.afsel().bits(FBV_ADC|AV_ADC));
        gpio_d.amsel.write(|w| w.amsel().bits(FBV_ADC|AV_ADC));
        gpio_e.afsel.write(|w| w.afsel().bits(FD_ADC|FV_ADC|FBI_ADC|IC_ADC));
        gpio_e.amsel.write(|w| w.amsel().bits(FD_ADC|FV_ADC|FBI_ADC|IC_ADC));

        sysctl.rcgcadc.modify(|_, w| w.r0().bit(true));
        while !sysctl.pradc.read().r0().bit() {}
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
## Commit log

2017-05-04 improve readme appearance
2017-05-04 smaller picture
2017-05-04 work around picture cache problems
2017-05-04 hello world
2017-05-04 LED access function
2017-05-04 drive both flyback PWMs
2017-05-04 use PWM functions
2017-05-04 Add FBV_PWM pin handling.
2017-05-04 set some FB potential
2017-05-04 set emission range
2017-05-04 add GDT200 errata
2017-05-04 add relay errata
2017-05-05 Add missing wait for GPIO ready.
2017-05-05 Move firmware to firmware/.
2017-05-05 Add schematics.
2017-05-05 Implement ADC readout.
2017-05-05 Move README.md back where it belongs.
2017-05-05 Also set AFSEL bits for pins where AMSEL is set.
2017-05-06 add Ethernet TVS and error latch errata
2017-05-06 fix gitignore
2017-05-06 get ADC samples as ints
2017-05-06 style
2017-05-06 Report error pin status
2017-05-06 HV PID control (untested)
2017-05-06 pid: use Option instead of NaN
2017-05-06 reset error latch at startup
2017-05-06 Unbreak ADC interrupt.
2017-05-06 Update errata.
2017-05-07 Enable PLL at 320 MHz.
2017-05-07 Make ADC actually work.
2017-05-07 Enable FPU.
2017-05-08 update dependencies
2017-05-08 Raise ADC clock to 32 MHz (maximum).
2017-05-08 some PID tuning
2017-05-08 put ADC in continuous sample mode
2017-05-08 speed up ADC
2017-05-09 Add UART debug port.
2017-05-09 reorganize
2017-05-09 remove unnecessary mut
2017-05-09 compute FV and FBV
2017-05-09 fix elapsed counter
2017-05-09 errata: glitches are ok, R234 should be changed
2017-05-09 print message on protection latch
2017-05-09 compute emission current, filament voltage and bias voltage
2017-05-09 average emission current samples, implement emission_ready
2017-05-10 fix resistor number in errata
2017-05-11 update FD_ADC_GAIN for new value of R234
2017-05-11 handle protection, print current/voltage values
2017-05-11 add electrometer, introduce *Status objects
2017-05-11 add license note
2017-05-12 update errata
2017-05-12 use PID for FV, print all debug messages
2017-05-13 adjust anode PID coefficients
2017-05-13 average more IC samples
2017-05-13 autoselect IC range
2017-05-16 add parameters for chinese ion gauges
2017-05-16 tweak emission PID parameters
2017-05-16 add missing PID update
2017-05-18 update readme, reorganize
2017-05-23 add value for C100
2017-05-31 fix R214 value
2017-05-31 add Gerber files
2017-05-31 update Gerber files
2017-06-06 README: add circular contact suggestion to connect to CF feedthroughs
2017-06-06 add shopping list
2017-06-07 add more pictures
2017-06-07 enlarge README picture
2017-06-08 clean up gauge parameters
2017-06-08 raise threshold for switching to more sensitive IC range
2017-06-12 increase clock frequency, enable FPU correctly
2017-07-04 add logo
2017-07-04 README: use logo
2017-07-04 Revert "README: use logo"
    GitHub won't serve SVG images correctly for some reason.
    This reverts commit d0889ed1f604571572fc269a4b65f0d7fa5fec53.
2017-07-04 add mechanical drawings
2017-07-22 add PDF enclosure silkscreen drawing
2017-07-24 add missing dimension on enclosure drawing
2017-07-24 add Kicad design files
2017-07-24 add BoM
2017-07-31 errata: filament flyback output diode
2017-07-31 add ethmac driver
2017-08-01 compile ethmac driver
2017-08-05 integrate ethmac/smoltcp (timestamp missing), add HTTP server
2017-08-05 superficial ethmac cleanup
2017-08-05 refactor ethmac
2017-08-06 convert ADC interrupt count to milliseconds
2017-08-06 start ADC after initialization, to avoid FIFO overflows
2017-08-06 flashed MAC address doesn't work
2017-08-06 print panic messages on UART
2017-08-06 work around ADC sample rate snafu
2017-08-06 remove GDB breakpoint at startup
2017-08-06 optimize electrometer averaging
2017-08-07 tweak cathode PID
2017-08-07 report target filament voltage
2017-08-07 report measurements on HTTP page
2017-08-07 fix TX buffer length in ethmac
2017-08-07 fix ethmac initialization
2017-08-07 detect invalid programmed MAC address
2017-08-07 get_time_ms: ADC sampling takes NSH+12 cycles and not NSH
2017-08-07 add EEPROM driver
2017-08-07 cleanup and integrate EEPROM driver
2017-08-07 configure Ethernet LED
2017-08-07 clean up index.html
2017-08-07 track firmware version and expose to HTTP
2017-08-07 add missing file from previous commit
2017-08-07 more eeprom cleanups, use u8 for buffer
2017-08-07 add config module
2017-08-08 config fixes
2017-08-08 implement support for HTTP GET arguments
2017-08-08 support setting IP address via web interface
2017-08-08 support resetting settings using pushbutton
2017-08-08 add JSON interface
2017-08-08 document usage
2017-09-05 update smoltcp
2017-09-09 README: add note about firewall
2017-09-25 do not use GDB for loading firmware
    GDB adds unnecessary steps and it is buggy.
2018-01-26 Update cargo-m-rt.
    Required for compatibility with newer rustc nightlies.
2018-01-26 Update to newer smoltcp.
    This also fixes a bug where RX descriptors would be first advanced
    and then released.
2018-01-29 Revert the rx_buf_release() change in 8491394a.
2018-01-29 Fix cmp::max/min mixup in 8491394a.
2018-02-12 add new pictures with enclosure
2018-03-08 remove broken mechanical design
2018-03-08 add rev2 hardware design
2018-03-08 remove 1U box from BS vendor from shopping list
2018-03-09 add rev2 paste gerber
2018-03-09 add rev2 BoM
2018-03-19 Revert "Revert the rx_buf_release() change in 8491394a."
    This reverts commit 724221c64378624c51468fabd944e4f608ec386b.
2018-03-19 openocd: use find instead of hardcoded paths
2018-03-26 Update firmware dependencies.
2018-03-26 Update smoltcp.
2018-03-26 Fix DMA writing to dangling pointers in ethmac.
2018-03-27 Fix signature of panic_fmt.
2018-03-27 Fix signature of panic_fmt even further.
2018-03-27 Rewrite ethmac to split ownership into RX/TX halves.
2018-03-27 Fix RxRing::buf_release.
    The original code was correct after all.
2018-03-27 Remove unnecessary unsafe blocks.
2018-03-27 Remove unused import.
2018-03-27 Unbreak network configuration page.
2018-03-27 Add Cache-Control header for static assets.
    This avoids wasting device cycles on retrieving the same data over
    and over.
2018-03-27 Use the crc crate.
2018-04-14 errata: add some rev2 changes
2018-04-14 errata: spelling
2018-08-28 Update for latest nightly.
2019-02-06 Update for Rust 1.32, and upgrade dependencies.
2019-02-06 Update README.
